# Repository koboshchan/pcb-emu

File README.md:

# pcb-emu

Reusable Python PCB circuit simulation, with physical KiCad copper extraction and explicit component models. Distribution `pcb-emu`, import `pcb_emu`. No SPICE dependency. This is an early behavioral emulator, not manufacturer silicon simulation or fabrication sign-off.

## Install

Python 3.11+, NumPy, SciPy and Shapely are required. KiCad's matching `pcbnew` Python module is needed only to load PCB files. Install KiCad separately; it is not a PyPI extra. Use the interpreter supplied with your KiCad installation when extracting boards.

```sh
python -m pip install -e '.[test]'
python -m pytest
```

## Boards, wiring and simulation

```python
from pcb_emu import Emulator

emu = Emulator(tick=1e-4)
board = emu.add_board('divider.kicad_pcb', name='sensor')
emu.drive(board.pin('R1', '1'), 5)
emu.drive(board.pin('R2', '2'), 0)
emu.dc()
print(emu.read(board.pin('R1', '2')))

def callback(snapshot):
    print(snapshot.tick, snapshot.time, snapshot.pin(board, 'R1', '2'))
    # Drives issued in a callback become active on the next tick.
    emu.drive(board.pin('R1', '1'), 3.3)

emu.run(ticks=100, callback=callback, substeps=10)
```

`Board(path, name)` loads one PCB. `Board(name=..., extracted=...)` accepts caller-supplied virtual circuit metadata. `examples/circuits.py` demonstrates that schema without requiring KiCad. PCB labels are diagnostic, not wires. No daughterboards, sources or jumpers are inserted automatically.

`emu.connect(pin_a, pin_b, resistance=...)` joins any two terminals. `emu.add_jumper(...)` uses the configurable jumper resistance. `emu.plug(board_a, header_ref, board_b, socket_ref, mapping=...)` connects complete connector maps, defaulting to matching pad numbers. Connections persist and recompile the node graph. `drive` accepts a voltage or function of simulated time. Pins can be `Pin` objects or `board.reference.pad` strings. `dc` finds an operating point; `run` advances capacitor and digital state. `Board.run()` is a convenience for a standalone board.

Snapshots share an immutable voltage array and pin index map. Callback frequency is once per tick regardless of substeps. Resolve waveform edges through sufficient substeps. Firmware execution is not cycle-accurate hardware emulation.

## Generic examples

`examples/analog.py` runs a resistor divider, noninverting amplifier and RC PWM filter. `examples/pico_ads1115.py` explicitly wires one Pico and one ADS1115 and reads a known analog voltage through trusted MicroPython-style firmware. Run them with `PYTHONPATH=src:examples python examples/analog.py` or `PYTHONPATH=src:examples python examples/pico_ads1115.py`.

## Models and numerical limitations

Supported components are resistors, capacitors, 1N4148W diodes, TL074 quad op amps, 74AHCT595 shift registers and L7805 regulators. Unknown electrical parts fail explicitly. Connector names and analog net labels carry no device-specific behavior.

The custom nodal solver uses SciPy sparse linear algebra, analytic diode/op-amp Jacobians, residual-tested line search and gain continuation. Capacitors use backward Euler. TL074 defaults have finite gain, smooth rail clipping and 50-ohm behavioral output resistance. These are approximations, not a validated transistor model. Convergence failures raise `ConvergenceError`; floating nodes receive 1 pS leakage. Zero-ohm resistors use a small numerical resistance.

AHCT595 implements serial shift, cascade, reset, output enable and latch. Digital ICs sample a shared old-state snapshot, so chain order cannot cause multiple shifts in one event. L7805 is a simplified dropout/regulated-voltage model.

## Copper and parasitics

Extraction intersects pads, tracks, vias and zones refilled in memory. Source files are SHA256 checked and never saved. Opposed SMD pads do not connect; through-hole pads and vias connect layers.

`ideal_copper=True` merges actual connected copper into ideal nodes, preserving finite connector/wire resistances. `ideal_copper=False` builds a distributed resistor graph. Exact copper-contact overlaps are merged before solving, while finite trace, via and connector resistances remain. Via barrels have a separate tap on each traversed copper layer, including blind/buried spans. Saved KiCad stackup thicknesses set copper layer depths and per-layer copper thickness; otherwise layers are uniformly spaced across the board thickness and copper defaults to 35 micrometers. Via plating and plane spreading are assumptions. Planes use star spreading resistance, not a field mesh. Connector contact and jumper defaults are 20 and 12 milliohms. Temperature affects copper resistivity. DNP/DNI/DNF values and KiCad DNP flags leave the physical pads present but omit the electrical component stamp.

Approximate trace/via capacitance and inductance inventories are not stamped into transient equations. Distributed RLC, transmission lines, skin effect, return-path coupling and thermal solving are not implemented.

## Supply, Pico and ADC

`emu.add_psu({'channel': 5}, current_limit=1, output_resistance=.01, ripple=0)` creates explicit `channel+`/`channel-` pins. Wire them, ground a return and call `psu.on()`. Channel dictionaries expose current, power and CV/CC mode. Ripple is sinusoidal. Simplified ICs do not consume realistic supply current.

`emu.add_pico(code='main.py')` or `source='...'` creates the real 40-pin Pico header. GP23–25 are not exposed. Alternatively pass an existing PCB footprint through `board` and `ref`. Trusted CPython executes MicroPython-style `machine`, `time`/`utime` and `rp2` APIs. Pin operations and sleeps rendezvous with simulation time. Watchdogs detect noncooperating loops. IRQ, PWM, ADC, SPI, I2C, UART and Timer interfaces are available. Buses require caller-installed callbacks in `pico.bus_handlers`; no device is invented. There is no substantial PIO implementation or RP2040 instruction simulation. Close the Pico after use.

`ADS1115(name=..., addr='GND').attach(emu)` provides A0–A3, VDD, GND, SDA, SCL and ADDR terminals. Addresses are selected by GND/VDD/SDA/SCL straps. `ADS1115Bus` bridges explicit Pico I2C transactions. Registers implement signed big-endian codes, MUX, PGA, nominal conversion periods and readiness. Comparator/ALERT requests fail explicitly. Inputs must remain within GND..VDD even when PGA full scale exceeds VDD.

ADC defaults use ideal input impedance, endpoint sampling and quantization, not switched-capacitor loading or delta-sigma history. Skipped continuous conversion periods sample current endpoint voltage. Electrical I2C edges, oscillator error and pull-up loading are absent.

## Seeded variations

`Variation(...).apply(emu, seed)` samples resistor/capacitor tolerances, TL074 offsets/bias/gain/GBW/slew, diode shift, regulator error, ambient effects and ADS1115 errors. Noise is frozen during each solve and deterministic at a given time. Use fresh boards for each physical sample. Run `PYTHONPATH=src:examples python examples/variation.py --samples 100` for a seeded divider Monte Carlo. See [VARIATION.md](VARIATION.md) for distributions, datasheet sources and the substantial behavioral assumptions. DC does not measure capacitor, bandwidth or slew sensitivity.

## CPU linear algebra

The simulator uses NumPy and SciPy CPU algebra. `pcb_emu.backend.ArrayBackend()` also supports reusable LU factors with multiple right-hand sides for callers that already have a linear matrix.

## Security

PCB files and firmware must be trusted. The CPython firmware runner is not a sandbox and executes with host permissions. Never execute untrusted code on a machine containing secrets. This project is distributed through GitHub; no automated package publication is configured.

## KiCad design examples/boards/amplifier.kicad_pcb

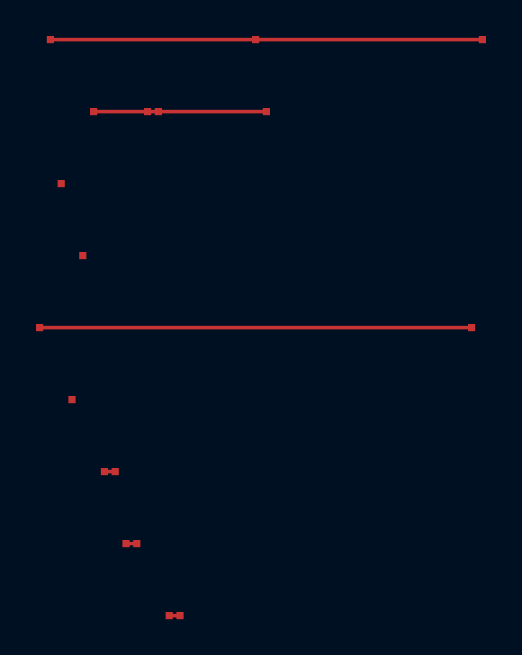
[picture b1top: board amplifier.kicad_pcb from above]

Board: 2 copper layers, 3 parts (0 on the bottom side), 6 nets.

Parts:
R1, R2: 10k
U1: TL074

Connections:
feedback: R1.1, R2.2, U1.2
ground: R1.2, U1.5, U1.10, U1.12
output: R2.1, U1.1
unused1: U1.6, U1.7
unused2: U1.8, U1.9
unused3: U1.13, U1.14
